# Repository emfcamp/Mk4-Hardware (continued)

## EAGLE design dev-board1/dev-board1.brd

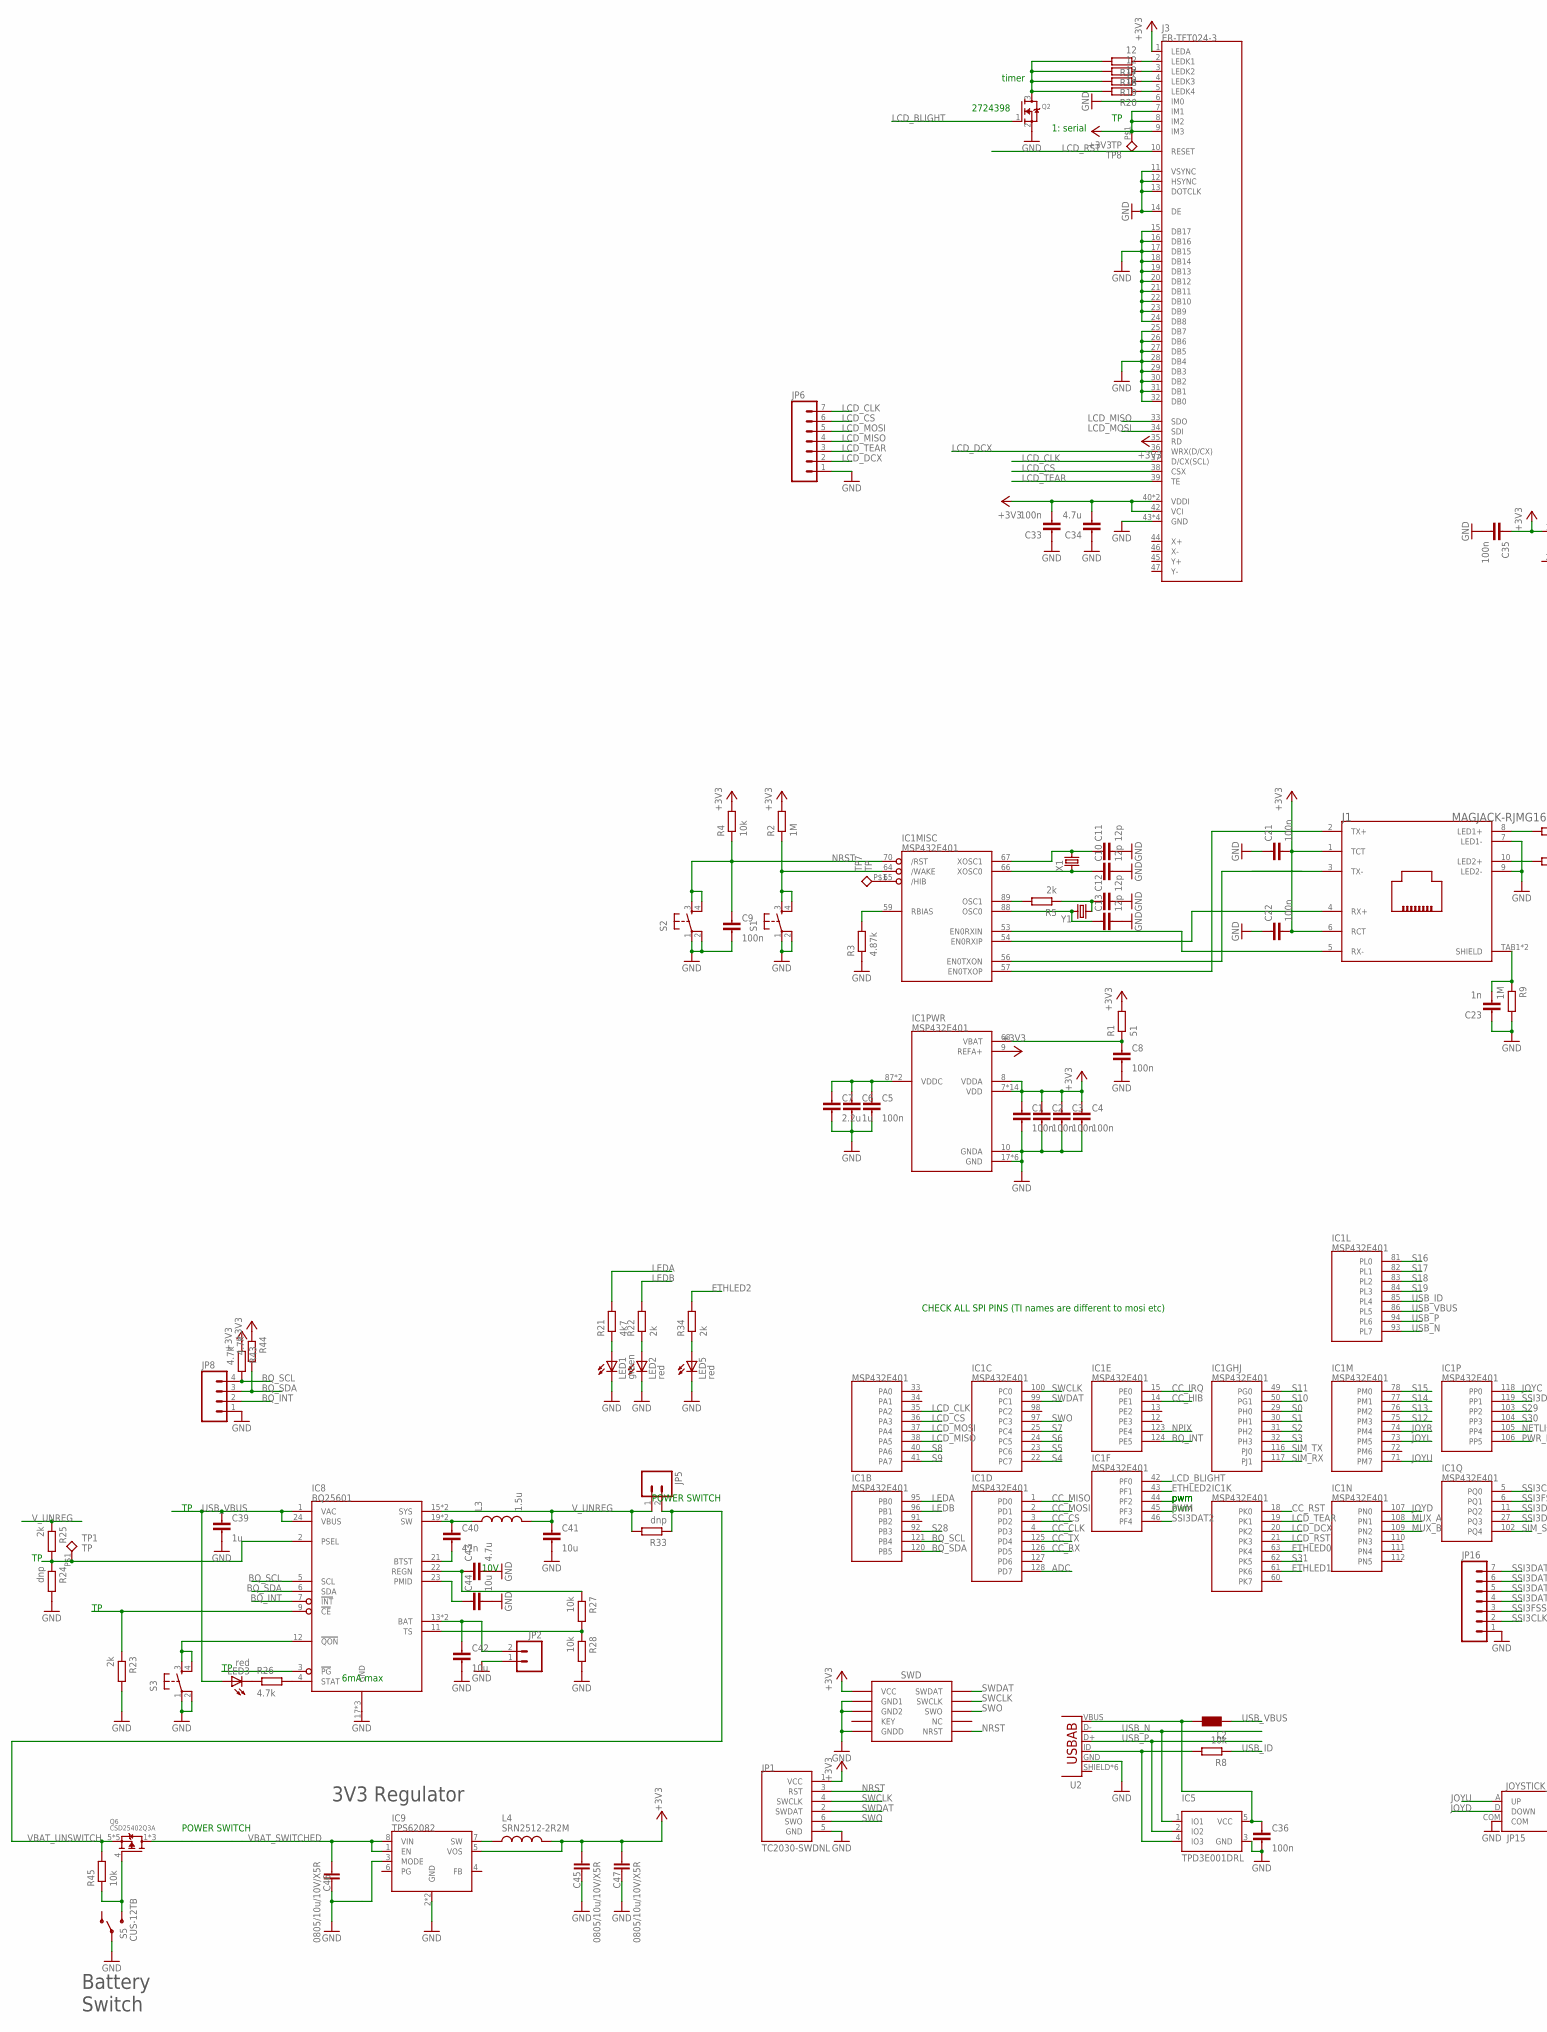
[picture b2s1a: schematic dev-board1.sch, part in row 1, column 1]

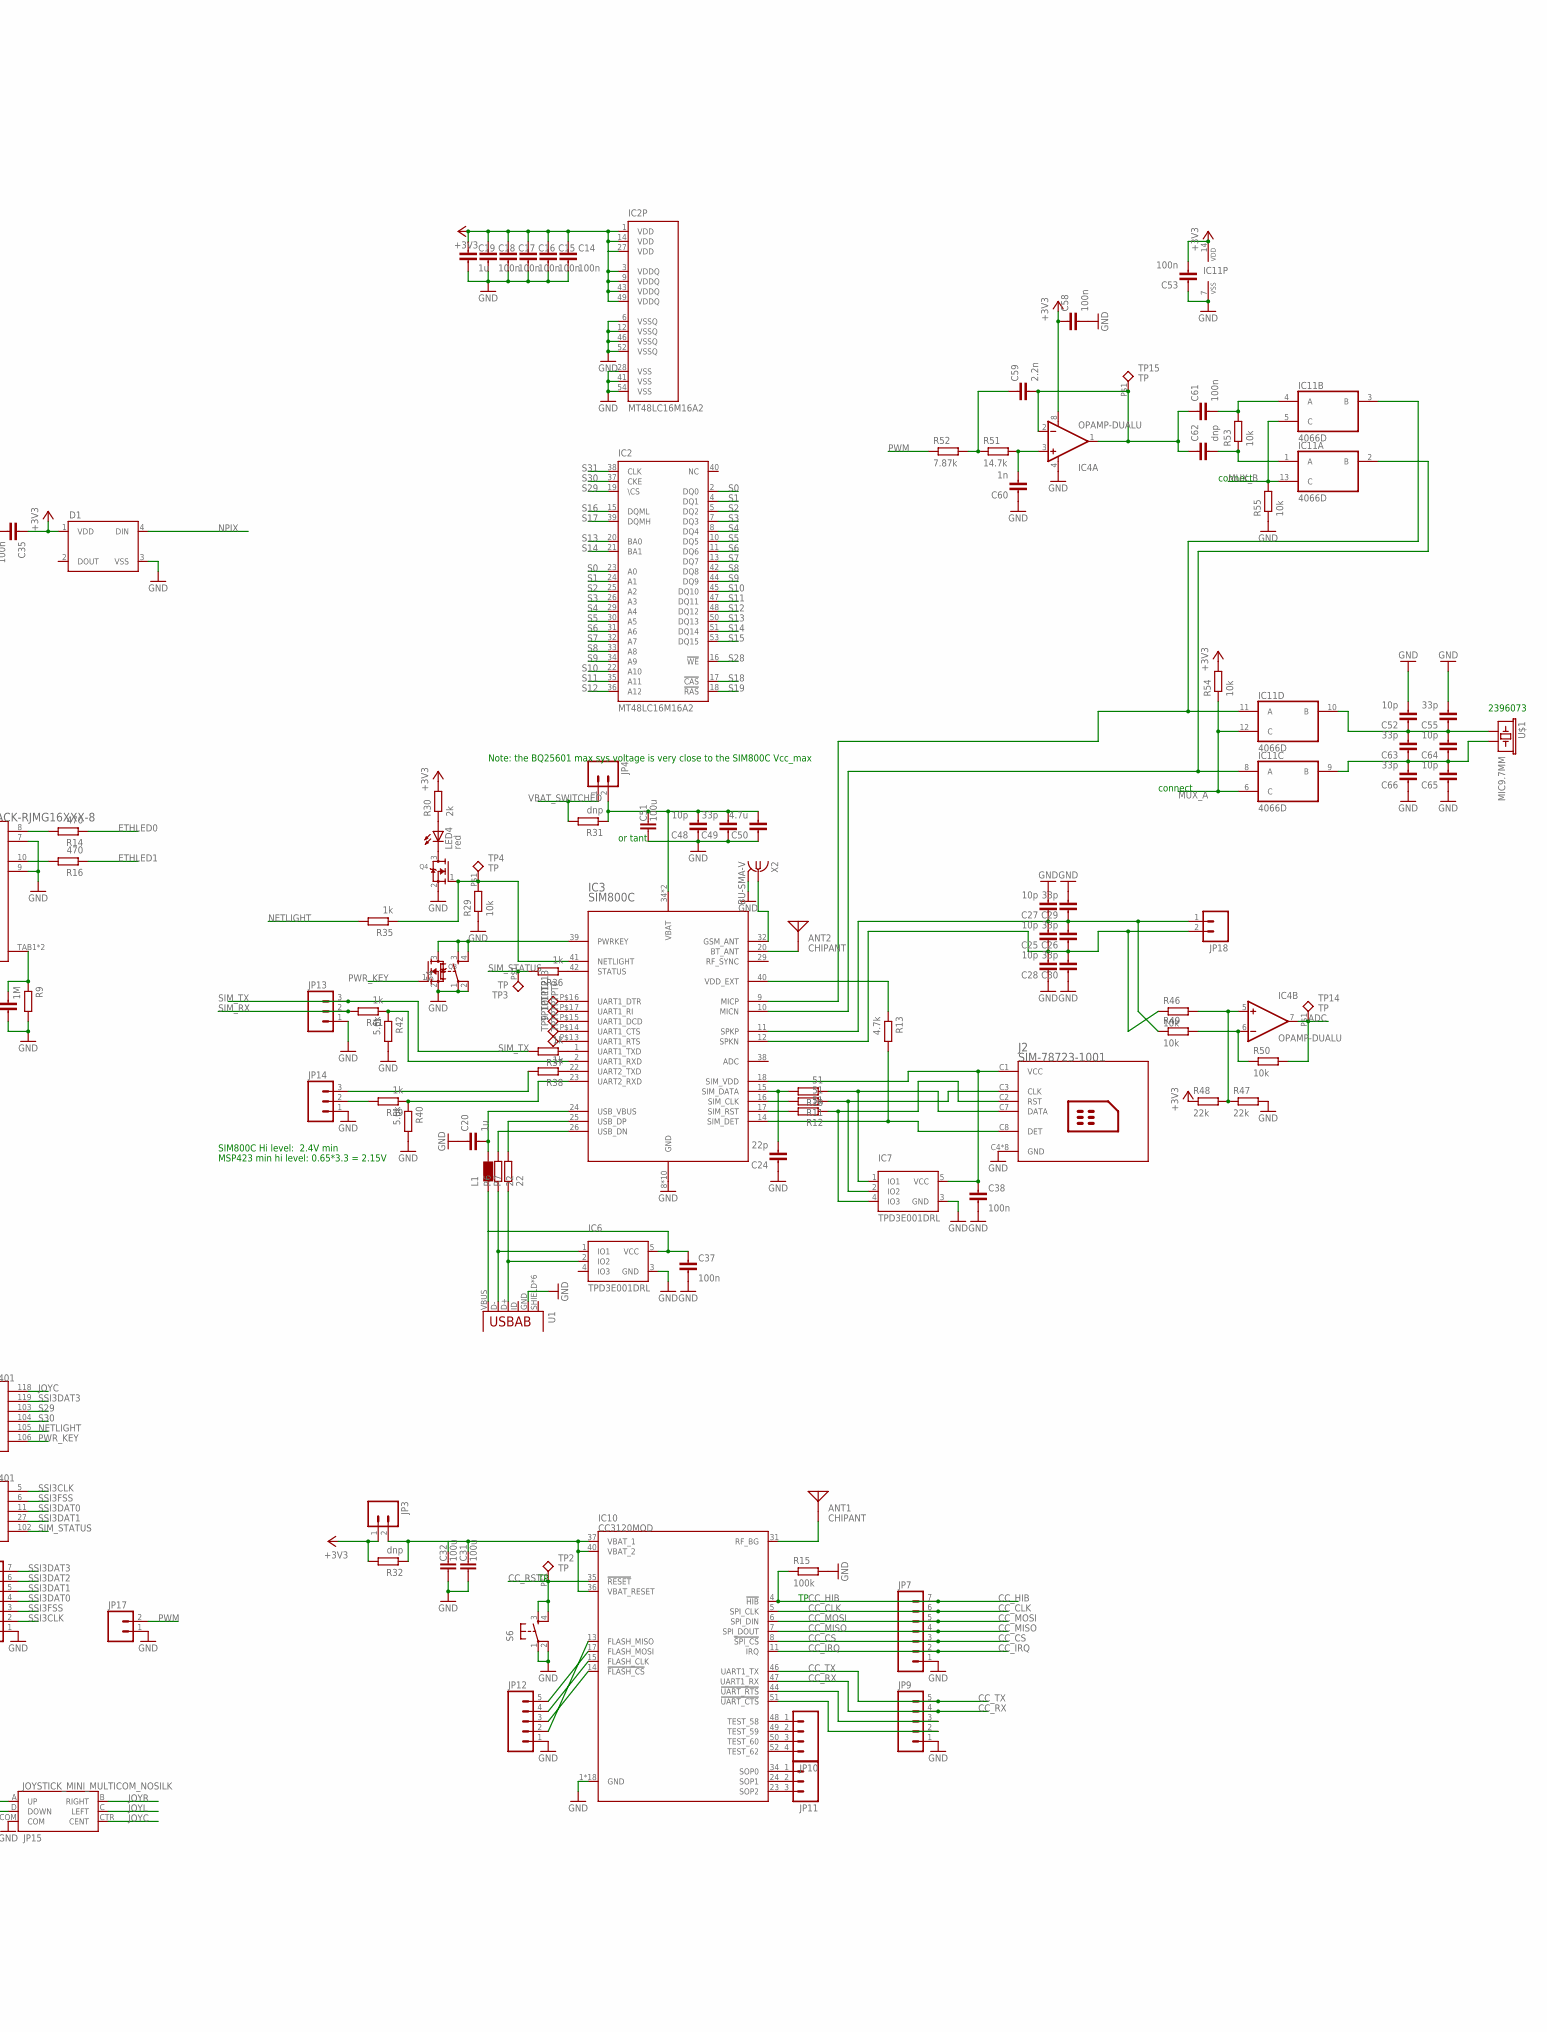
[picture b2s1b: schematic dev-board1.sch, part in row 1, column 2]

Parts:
ANT1, ANT2: CHIPANT; 2450AT42A100; FARNELL 2148522
C1, C2, C3, C4, C5, C8, C9, C14, C15, C16, C17, C18, C21, C22, C33, C35, C36, C37, C38, C53, C58, C61: 100n; C0603-N
C6, C19, C20, C39: 1u; C0603-N
C7: 2.2u; C0603-N
C10, C11, C12, C13: 12p; C0603-N
C23, C60: 1n; C0603-N
C24: 22p; C0603-N
C25, C27, C28, C48, C52, C64, C65: 10p; C0603-N
C26, C29, C30, C49, C55, C63, C66: 33p; C0603-N
C31, C32, C51: 100u; C1210; FARNELL 1889302
C34, C43, C50: 4.7u; C0603-N; FARNELL 2524873
C40: 47n; C0603-N
C41, C42, C44: 10u; C0805-N; FARNELL 2112853/2362101/2576756
C45, C46, C47: 0805/10u/10V/X5R; C0805-N; FARNELL 2112853/2362101/2576756
C59: 2.2n; C0603-N
C62: dnp; C0603-N
D1: WS2812B
IC1: MSP432E401; QFP128-0.4
IC2: MT48LC16M16A2; TSOP54-400; FARNELL 2253738
IC3: SIM800C
IC4: OPAMP-DUALU; SO08; FARNELL 2463666
IC5, IC6, IC7: TPD3E001DRL; DRL-5
IC8: BQ25601; QFN-24
IC9: TPS62082; WSON8; FARNELL 2064227
IC10: CC3120MOD; CC3100MOD-LWK
IC11: 4066D; SO14; FARNELL 1201330
J1: MAGJACK-RJMG16XXX-8; RJMG163118101NR; FARNELL 1357436
J2: SIM-78723-1001; MSIM-MOLEX; FARNELL 2213306
J3: ER-TFT024-3; FH12-50S-0.5SH
J4: SWD_SHROUD; SWD_PTH_SHROUD; FARNELL 1865285
JP1: TC2030-SWDNL; TC2030-MCP-NL
JP2: M02-JST-2MM-SMT; JST-2-SMD; FARNELL 9492615
JP3, JP4, JP5, JP17, JP18: M02PTH; 1X02
JP6, JP7, JP16: M07; 1X07
JP8, JP10: M04PTH; 1X04
JP9, JP12: M05PTH; 1X05
JP11, JP13, JP14: M03PTH; 1X03
JP15: JOYSTICK_MINI_MULTICOM_NOSILK; JOYSTICK_MULTICOMP_NOSILK; FARNELL 1316987
L1, L2: WE-CBF_0805; WUERTH-0805; FARNELL 1781089
L3: 1.5u; 1008; FARNELL 2428202
L4: SRN2512-2R2M; 1008; FARNELL 2428203
LED1: green; LED-0603; FARNELL 2426215
LED2, LED3, LED4, LED5: red; LED-0603; FARNELL 2449874
Q2: MOSFET-N-SOT23-SPARK; SOT23-3; FARNELL 2724398
Q3, Q4: MOSFET-N-SOT23-SPARK; SOT23-3
Q6: CSD25402Q3A; Q3A; FARNELL 2501103
R1, R10, R11, R12: 51; R0603-N
R2, R9: 1M; R0603-N
R3: 4.87k; R0603-N; FARNELL 2447387
R4, R8, R27, R28, R29, R45, R46, R49, R50, R53, R54, R55: 10k; R0603-N
R5, R22, R23, R25, R30, R34: 2k; R0603-N
R6, R7: 22; R0603-N
R13, R26, R43, R44: 4.7k; R0603-N
R14, R16: 470; R0603-N
R15: 100k; R0603-N
R17, R18, R19, R20: 12; R0603-N
R21: 4k7; R0603-N
R24, R31, R32, R33: dnp; R0603-N
R35, R36, R37, R38, R39, R41: 1k; R0603-N
R40, R42: 5.6k; R0603-N
R47, R48: 22k; R0603-N
R51: 14.7k; R0603-N
R52: 7.87k; R0603-N
S1, S2, S3, S4, S6: 6MMTACTSMSM; 6MMTACTSM; FARNELL 2320087
S5: CUS-12TB; SWITCH-SPST-SMD-A; FARNELL 9575146
TP1, TP2, TP3, TP4, TP7, TP8, TP9, TP10, TP11, TP12, TP13, TP14, TP15: TP
U1, U2: USB-AB-LWK; USB-AB-MICRO-SMD_LWK; FARNELL 2293755
U$1: MIC9.7MM; MIC-9.7MM; FARNELL 2396073
X1: RESONATOR_EPSON_FC_145; FARNELL 2723239
X2: BU-SMA-V; FARNELL 1248990
Y1: CRYSTAL5X3; CRYSTAL-SMD-5X3; FARNELL 2508925

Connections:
+3V3: C1.1, C2.1, C3.1, C4.1, C14.1, C15.1, C16.1, C17.1, C18.1, C19.1, C21.2, C22.2, C33.2, C34.2, C35.1, C45.1, C47.1, C53.2, C58.1, D1.1 (VDD), IC1.7 (VDD), IC1.8 (VDDA), IC1.9 (REFA+), IC1.16 (VDD), IC1.26 (VDD), IC1.28 (VDD), IC1.39 (VDD), IC1.47 (VDD), IC1.51 (VDD), IC1.52 (VDD), IC1.69 (VDD), IC1.79 (VDD), IC1.90 (VDD), IC1.101 (VDD), IC1.113 (VDD), IC1.122 (VDD), IC2.1 (VDD), IC2.3 (VDDQ), IC2.9 (VDDQ), IC2.14 (VDD), IC2.27 (VDD), IC2.43 (VDDQ), IC2.49 (VDDQ), IC4.8 (V+), IC9.5 (VOS), IC11.14 (VDD), J1.1 (TCT), J1.6 (RCT), J3.1 (LEDA), J3.7 (IM1), J3.8 (IM2), J3.9 (IM3), J3.35 (RD), J3.40 (VDDI), J3.41 (VDDI), J3.42 (VCI), J4.1 (VCC), JP1.1 (VCC), JP3.1, L4.2, R1.2, R2.2, R4.2, R30.2, R32.2, R43.1, R44.1, R48.1, R54.2, TP8.P$1
ADC: IC1.128 (PD7), IC4.7 (OUT), R50.2, TP14.P$1
BQ_INT: IC1.124 (PE5), IC8.7 (!INT), JP8.2
BQ_SCL: IC1.121 (PB4), IC8.5 (SCL), JP8.4, R43.2
BQ_SDA: IC1.120 (PB5), IC8.6 (SDA), JP8.3, R44.2
CC_CLK: IC1.4 (PD3), IC10.5 (SPI_CLK), JP7.6
CC_CS: IC1.3 (PD2), IC10.8 (!SPI_CS), JP7.3
CC_HIB: IC1.14 (PE1), IC10.4 (!HIB), JP7.7, R15.1
CC_IRQ: IC1.15 (PE0), IC10.11 (IRQ), JP7.2
CC_MISO: IC1.1 (PD0), IC10.7 (SPI_DOUT), JP7.4
CC_MOSI: IC1.2 (PD1), IC10.6 (SPI_DIN), JP7.5
CC_RST: IC1.18 (PK0), IC10.35 (!RESET), S6.3, S6.4, TP2.P$1
CC_RX: IC1.126 (PD5), IC10.47 (UART1_RX), JP9.4
CC_TX: IC1.125 (PD4), IC10.46 (UART1_TX), JP9.5
ETHLED0: IC1.63 (PK4), R14.1
ETHLED1: IC1.61 (PK6), R16.1
ETHLED2: IC1.43 (PF1), R34.2
GGGG: IC3.2 (UART1_RXD), R41.1, R42.1
GND: C1.2, C2.2, C3.2, C4.2, C5.2, C6.2, C7.2, C8.2, C9.2, C10.2, C11.2, C12.2, C13.2, C14.2, C15.2, C16.2, C17.2, C18.2, C19.2, C20.1, C21.1, C22.1, C23.1, C24.1, C27.2, C28.1, C29.2, C30.1, C31.2, C32.2, C33.1, C34.1, C35.2, C36.2, C37.2, C38.2, C39.2, C41.2, C42.2, C43.2, C44.2, C45.2, C46.2, C47.2, C48.1, C49.1, C50.1, C51.2, C52.2, C53.1, C55.2, C58.2, C60.1, C65.1, C66.1, D1.3 (VSS), IC1.10 (GNDA), IC1.17 (GND), IC1.48 (GND), IC1.55 (GND), IC1.58 (GND), IC1.80 (GND), IC1.114 (GND), IC2.6 (VSSQ), IC2.12 (VSSQ), IC2.28 (VSS), IC2.41 (VSS), IC2.46 (VSSQ), IC2.52 (VSSQ), IC2.54 (VSS), IC3.8 (GND), IC3.13 (GND), IC3.19 (GND), IC3.21 (GND), IC3.27 (GND), IC3.30 (GND), IC3.31 (GND), IC3.33 (GND), IC3.36 (GND), IC3.37 (GND), IC4.4 (V-), IC5.3 (GND), IC6.3 (GND), IC7.3 (GND), IC8.17 (GND), IC8.18 (GND), IC8.25 (GND), IC9.2 (GND), IC9.3 (MODE), IC9.EP (GND), IC10.1 (GND), IC10.2 (GND), IC10.16 (GND), IC10.27 (GND), IC10.28 (GND), IC10.30 (GND), IC10.32 (GND), IC10.38 (GND), IC10.43 (GND), IC10.55 (GND), IC10.56 (GND), IC10.57 (GND), IC10.58 (GND), IC10.59 (GND), IC10.60 (GND), IC10.61 (GND), IC10.62 (GND), IC10.63 (GND), IC11.7 (VSS), J1.7 (LED1-), J1.9 (LED2-), J2.C4 (GND), J2.C5 (GND), J2.GND1 (GND), J2.GND2 (GND), J2.GND3 (GND), J2.GND4 (GND), J2.GND5 (GND), J2.GND6 (GND), J3.6 (IM0), J3.11 (VSYNC), J3.12 (HSYNC), J3.13 (DOTCLK), J3.14 (DE), J3.15 (DB17), J3.16 (DB16), J3.17 (DB15), J3.18 (DB14), J3.19 (DB13), J3.20 (DB12), J3.21 (DB11), J3.22 (DB10), J3.23 (DB9), J3.24 (DB8), J3.25 (DB7), J3.26 (DB6), J3.27 (DB5), J3.28 (DB4), J3.29 (DB3), J3.30 (DB2), J3.31 (DB1), J3.32 (DB0), J3.43 (GND), J3.48 (GND), J3.49 (GND), J3.50 (GND), J4.3 (GND1), J4.5 (GND2), J4.9 (GNDD), JP1.5 (GND), JP2.1, JP6.1, JP7.1, JP8.1, JP9.1, JP12.1, JP13.1, JP14.1, JP15.COM, JP16.1, JP17.1, LED1.C, LED2.C, LED5.C, Q2.2 (S), Q3.2 (S), Q4.2 (S), R3.1, R9.2, R15.2, R23.2, R24.2, R28.2, R29.1, R40.2, R42.2, R47.2, R55.1, S1.1, S1.2, S2.1, S2.2, S3.1, S3.2, S4.1, S4.2, S5.2, S6.1, S6.2, U1.GND, U2.GND, X2.2, X2.3 (2), X2.4 (2), X2.5 (2)
JOYC: IC1.118 (PP0), JP15.CTR (CENT)
JOYD: IC1.107 (PN0), JP15.D (DOWN)
JOYL: IC1.73 (PM5), JP15.C (LEFT)
JOYR: IC1.74 (PM4), JP15.B (RIGHT)
JOYU: IC1.71 (PM7), JP15.A (UP)
LCD_BLIGHT: IC1.42 (PF0), Q2.1 (G)
LCD_CLK: IC1.35 (PA2), J3.37 (D/CX(SCL)), JP6.7
LCD_CS: IC1.36 (PA3), J3.38 (CSX), JP6.6
LCD_DCX: IC1.20 (PK2), J3.36 (WRX(D/CX)), JP6.2
LCD_MISO: IC1.38 (PA5), J3.33 (SDO), JP6.4
LCD_MOSI: IC1.37 (PA4), J3.34 (SDI), JP6.5
LCD_RST: IC1.21 (PK3), J3.10 (RESET)
LCD_TEAR: IC1.19 (PK1), J3.39 (TE), JP6.3
LEDA: IC1.95 (PB0), R21.2
LEDB: IC1.96 (PB1), R22.2
MUX_A: IC1.108 (PN1), IC11.6 (C), IC11.12 (C), R54.1
MUX_B: IC1.109 (PN2), IC11.5 (C), IC11.13 (C), R55.2
unnamed: IC1.89 (OSC1), R5.2
unnamed: C5.1, C6.1, C7.1, IC1.87 (VDDC), IC1.115 (VDDC)
unnamed: C42.1, IC8.13 (BAT), IC8.14 (BAT), JP2.2
unnamed: C12.1, R5.1, Y1.1
unnamed: C13.1, IC1.88 (OSC0), Y1.3 (2)
unnamed: C10.1, IC1.66 (XOSC0), X1.P$1 (1)
unnamed: C8.1, IC1.68 (VBAT), R1.1
unnamed: C11.1, IC1.67 (XOSC1), X1.P$2 (2)
unnamed: IC1.64 (/WAKE), R2.1, S1.3, S1.4
unnamed: IC6.1 (IO1), R6.1, U1.D-
unnamed: IC1.59 (RBIAS), R3.2
unnamed: IC3.32 (GSM_ANT), X2.1
unnamed: IC6.2 (IO2), R7.1, U1.D+
unnamed: IC3.25 (USB_DP), R7.2
unnamed: IC3.26 (USB_DN), R6.2
unnamed: IC5.4 (IO3), R8.2, U2.ID (USBID)
unnamed: C36.1, IC5.5 (VCC), L2.2, U2.VBUS
unnamed: C20.2, IC3.24 (USB_VBUS), L1.2
unnamed: C37.1, IC6.5 (VCC), L1.1, U1.VBUS
unnamed: IC1.53 (EN0RXIN), J1.5 (RX-)
unnamed: IC1.54 (EN0RXIP), J1.4 (RX+)
unnamed: IC1.56 (EN0TXON), J1.3 (TX-)
unnamed: IC1.57 (EN0TXOP), J1.2 (TX+)
unnamed: C23.2, J1.TAB1 (SHIELD), J1.TAB2 (SHIELD), R9.1
unnamed: J1.8 (LED1+), R14.2
unnamed: J1.10 (LED2+), R16.2
unnamed: C24.2, IC3.15 (SIM_DATA), R10.2
unnamed: IC3.16 (SIM_CLK), R11.2
unnamed: IC3.17 (SIM_RST), R12.2
unnamed: IC7.1 (IO1), J2.C7 (DATA), R10.1
unnamed: IC7.2 (IO2), J2.C3 (CLK), R11.1
unnamed: IC7.4 (IO3), J2.C2 (RST), R12.1
unnamed: IC3.14 (SIM_DET), J2.C8 (DET), R13.2
unnamed: IC3.40 (VDD_EXT), R13.1
unnamed: C38.1, IC3.18 (SIM_VDD), IC7.5 (VCC), J2.C1 (VCC)
unnamed: IC4.5 (+IN), R46.2, R47.1, R48.2
unnamed: IC3.9 (MICP), IC11.3 (B), IC11.11 (A)
unnamed: LED5.A, R34.1
unnamed: C25.2, C26.2, C27.1, C29.1, IC3.11 (SPKP), JP18.1, R49.1
unnamed: C25.1, C26.1, C28.2, C30.2, IC3.12 (SPKN), JP18.2, R46.1
unnamed: IC3.10 (MICN), IC11.2 (B), IC11.8 (A)
unnamed: IC10.48 (TEST_58), JP10.1
unnamed: IC10.44 (!UART_RTS), JP9.3
unnamed: C48.2, C49.2, C50.2, C51.1, IC3.34 (VBAT), IC3.35 (VBAT), JP4.2, R31.1
unnamed: LED4.C, Q4.3 (D)
unnamed: ANT1.P$1, IC10.31 (RF_BG)
unnamed: IC10.51 (!UART_CTS), JP9.2
unnamed: C31.1, C32.1, IC10.36 (VBAT_RESET), IC10.37 (VBAT_1), IC10.40 (VBAT_2), JP3.2, R32.1
unnamed: IC10.49 (TEST_59), JP10.2
unnamed: IC10.50 (TEST_60), JP10.3
unnamed: IC3.39 (PWRKEY), Q3.3 (D), S4.3, S4.4
unnamed: IC10.52 (TEST_62), JP10.4
unnamed: IC10.34 (SOP0), JP11.1
unnamed: J3.2 (LEDK1), R17.1
unnamed: J3.3 (LEDK2), R18.1
unnamed: J3.4 (LEDK3), R19.1
unnamed: J3.5 (LEDK4), R20.1
unnamed: Q2.3 (D), R17.2, R18.2, R19.2, R20.2
unnamed: IC10.24 (SOP1), JP11.2
unnamed: ANT2.P$1, IC3.20 (BT_ANT)
unnamed: C40.1, IC8.19 (SW), IC8.20 (SW), L3.1
unnamed: LED4.A, R30.1
unnamed: IC10.23 (SOP2), JP11.3
unnamed: IC10.15 (FLASH_CLK), JP12.4
unnamed: LED1.A, R21.1
unnamed: LED2.A, R22.1
unnamed: IC10.14 (!FLASH_CS), JP12.3
unnamed: IC10.17 (FLASH_MOSI), JP12.5
unnamed: IC10.13 (FLASH_MISO), JP12.2
unnamed: IC3.22 (UART2_TXD), R38.1
unnamed: C40.2, IC8.21 (BTST)
unnamed: C43.1, IC8.22 (REGN), R27.1
unnamed: C44.1, IC8.23 (PMID)
unnamed: IC8.12 (!QON), S3.3, S3.4
unnamed: JP14.3, R38.2
unnamed: IC8.9 (!CE), R23.1
unnamed: IC8.2 (PSEL), R24.1, R25.2, TP1.P$1
unnamed: IC1.65 (/HIB), TP7.P$1
unnamed: C63.1, C64.1, C65.2, C66.2, IC11.9 (B), U$1.2
unnamed: IC3.42 (STATUS), R36.1
unnamed: IC8.4 (STAT), R26.2
unnamed: LED3.C, R26.1
unnamed: IC8.11 (TS), R27.2, R28.1
unnamed: IC4.6 (-IN), R49.2, R50.1
unnamed: C59.2, C61.1, C62.1, IC4.1 (OUT), IC4.2 (-IN), TP15.P$1
unnamed: IC3.1 (UART1_TXD), R37.1
unnamed: IC3.23 (UART2_RXD), R39.1, R40.1
unnamed: JP14.2, R39.2
unnamed: IC3.3 (UART1_RTS), TP9.P$1
unnamed: IC3.4 (UART1_CTS), TP10.P$1
unnamed: IC3.5 (UART1_DCD), TP11.P$1
unnamed: IC3.7 (UART1_RI), TP12.P$1
unnamed: IC3.6 (UART1_DTR), TP13.P$1
unnamed: C60.2, IC4.3 (+IN), R51.2
unnamed: C59.1, R51.1, R52.2
unnamed: C61.2, IC11.4 (A), R53.2
unnamed: C62.2, IC11.1 (A), R53.1
unnamed: C52.1, C55.1, C63.2, C64.2, IC11.10 (B), U$1.1
NETLIGHT: IC1.105 (PP4), R35.2
NETLIGHT_: IC3.41 (NETLIGHT), Q4.1 (G), R29.2, R35.1, TP4.P$1
NPIX: D1.4 (DIN), IC1.123 (PE4)
NRST: C9.1, IC1.70 (/RST), J4.10 (NRST), JP1.3 (RST), R4.1, S2.3, S2.4
PWM: IC1.45 (PF3), JP17.2, R52.1
PWR_KEY: IC1.106 (PP5), Q3.1 (G)
S0: IC1.29 (PH0), IC2.2 (DQ0), IC2.23 (A0)
S1: IC1.30 (PH1), IC2.4 (DQ1), IC2.24 (A1)
S2: IC1.31 (PH2), IC2.5 (DQ2), IC2.25 (A2)
S3: IC1.32 (PH3), IC2.7 (DQ3), IC2.26 (A3)
S4: IC1.22 (PC7), IC2.8 (DQ4), IC2.29 (A4)
S5: IC1.23 (PC6), IC2.10 (DQ5), IC2.30 (A5)
S6: IC1.24 (PC5), IC2.11 (DQ6), IC2.31 (A6)
S7: IC1.25 (PC4), IC2.13 (DQ7), IC2.32 (A7)
S8: IC1.40 (PA6), IC2.33 (A8), IC2.42 (DQ8)
S9: IC1.41 (PA7), IC2.34 (A9), IC2.44 (DQ9)
S10: IC1.50 (PG1), IC2.22 (A10), IC2.45 (DQ10)
S11: IC1.49 (PG0), IC2.35 (A11), IC2.47 (DQ11)
S12: IC1.75 (PM3), IC2.36 (A12), IC2.48 (DQ12)
S13: IC1.76 (PM2), IC2.20 (BA0), IC2.50 (DQ13)
S14: IC1.77 (PM1), IC2.21 (BA1), IC2.51 (DQ14)
S15: IC1.78 (PM0), IC2.53 (DQ15)
S16: IC1.81 (PL0), IC2.15 (DQML)
S17: IC1.82 (PL1), IC2.39 (DQMH)
S18: IC1.83 (PL2), IC2.17 (!CAS)
S19: IC1.84 (PL3), IC2.18 (!RAS)
S28: IC1.92 (PB3), IC2.16 (!WE)
S29: IC1.103 (PP2), IC2.19 (\CS)
S30: IC1.104 (PP3), IC2.37 (CKE)
S31: IC1.62 (PK5), IC2.38 (CLK)
SIM_RX: IC1.117 (PJ1), JP13.2, R41.2
SIM_STATUS: IC1.102 (PQ4), R36.2, TP3.P$1
SIM_TX: IC1.116 (PJ0), JP13.3, R37.2
SSI3CLK: IC1.5 (PQ0), JP16.2
SSI3DAT0: IC1.11 (PQ2), JP16.4
SSI3DAT1: IC1.27 (PQ3), JP16.5
SSI3DAT2: IC1.46 (PF4), JP16.6
SSI3DAT3: IC1.119 (PP1), JP16.7
SSI3FSS: IC1.6 (PQ1), JP16.3
SW: IC9.7 (SW), L4.1
SWCLK: IC1.100 (PC0), J4.4 (SWCLK), JP1.4 (SWCLK)
SWDAT: IC1.99 (PC1), J4.2 (SWDAT), JP1.2 (SWDAT)
SWO: IC1.97 (PC3), J4.6 (SWO), JP1.6 (SWO)
USB_ID: IC1.85 (PL4), R8.1
USB_N: IC1.93 (PL7), IC5.1 (IO1), U2.D-
USB_P: IC1.94 (PL6), IC5.2 (IO2), U2.D+
USB_VBUS: C39.1, IC1.86 (PL5), IC8.1 (VAC), IC8.24 (VBUS), L2.1, LED3.A
VBAT_SWITCHED: C46.1, IC9.1 (EN), IC9.8 (VIN), JP4.1, Q6.1 (D), Q6.2 (D), Q6.3 (D), R31.2
VBAT_SWITCH_CONTROL: Q6.4 (G), R45.1, S5.3 (S)
VBAT_UNSWITCH: JP5.2, Q6.5 (S), Q6.6 (S), Q6.7 (S), Q6.8 (S), Q6.EP (S), R33.1, R45.2
V_UNREG: C41.1, IC8.15 (SYS), IC8.16 (SYS), JP5.1, L3.2, R25.1, R33.2

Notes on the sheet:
timer
1: serial
3V3 Regulator
10V
6mA max
POWER SWITCH
Battery Switch
CHECK ALL SPI PINS (TI names are different to mosi etc)
or tant
2396073
2724398
SIM800C Hi level: 2.4V min
MSP423 min hi level: 0.65*3.3 = 2.15V
Note: the BQ25601 max sys voltage is very close to the SIM800C Vcc_max
pwm
connect

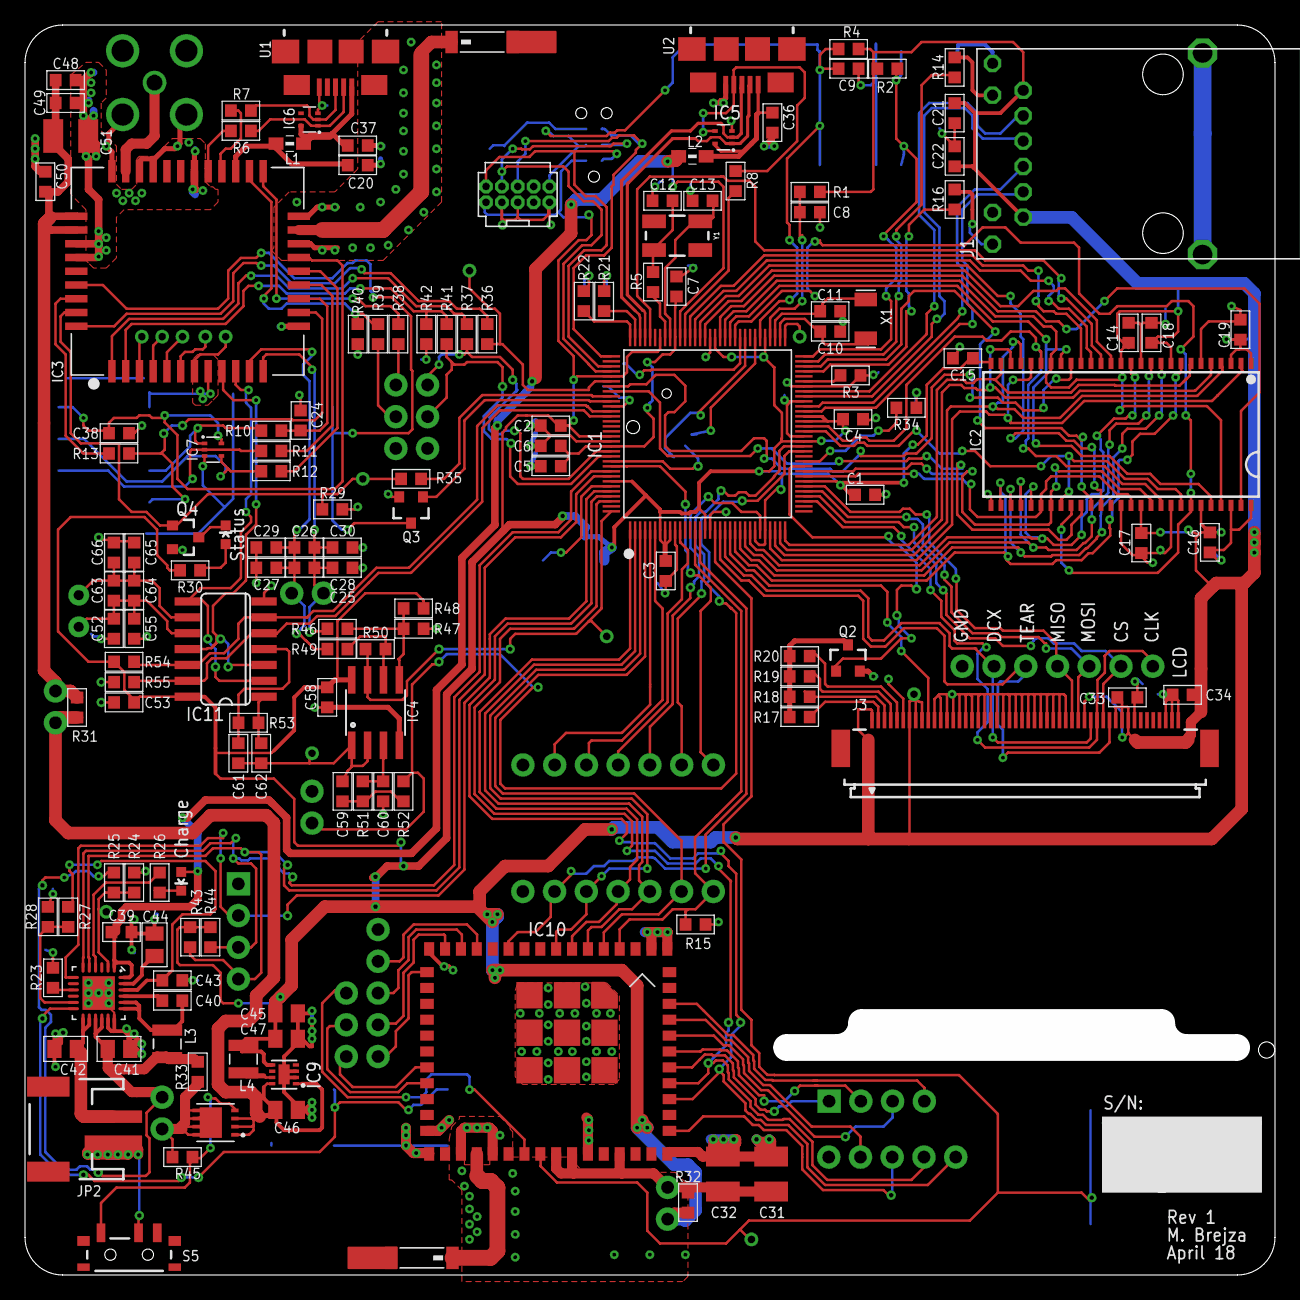
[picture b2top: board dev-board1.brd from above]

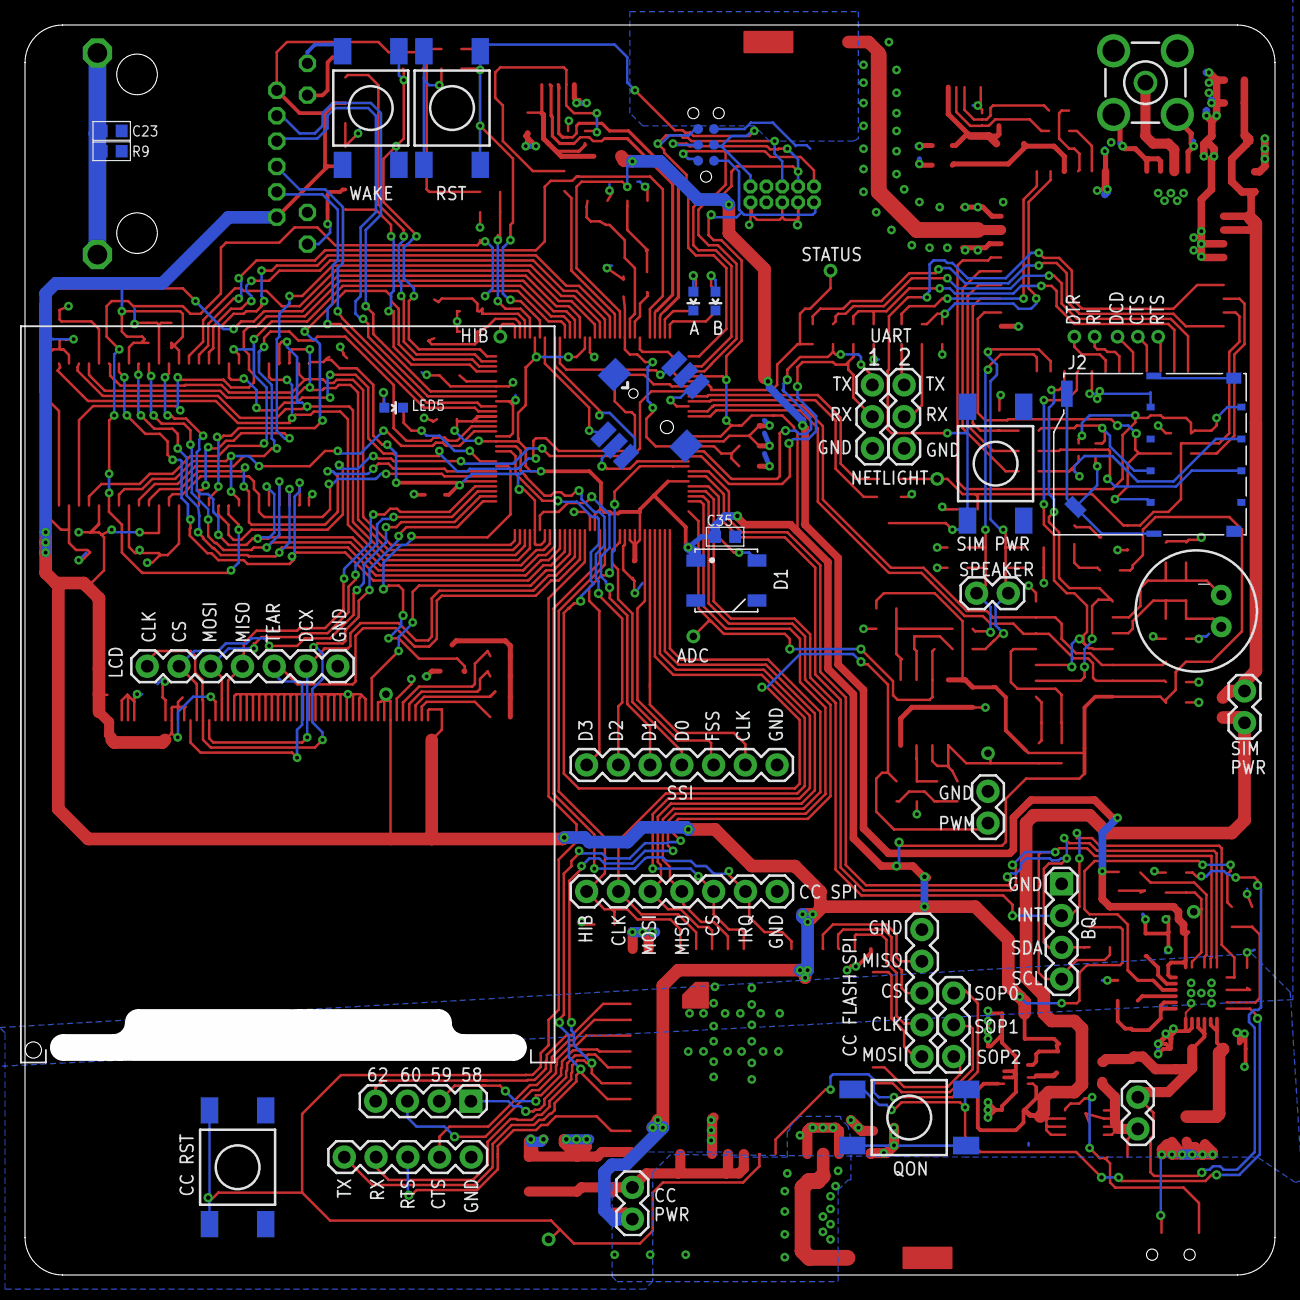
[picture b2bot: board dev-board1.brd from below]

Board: 2 copper layers, 100.0 x 100.0 mm, 193 parts (36 on the bottom side), 185 nets.

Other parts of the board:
U3: ER-TFT024-3-OUTLINE; ER-TFT024-3

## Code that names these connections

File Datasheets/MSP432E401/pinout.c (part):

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	GPIOD->GPIO_O_LOCK = 0x0;
	
    //
    // Configure the GPIO Pin Mux for PD7
	// for AIN4
    //
	MAP_GPIOPinTypeADC(GPIO_PORTD_BASE, GPIO_PIN_7);
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	GPIOPinTypeEPI(GPIO_PORTL_BASE, GPIO_PIN_0);

    //
    // Configure the GPIO Pin Mux for PG0
	// for EPI0S11
    //
	MAP_GPIOPinConfigure(GPIO_PG0_EPI0S11);
	GPIOPinTypeEPI(GPIO_PORTG_BASE, GPIO_PIN_0);

    //
    // Configure the GPIO Pin Mux for PA6
	// for EPI0S8
    //
	MAP_GPIOPinConfigure(GPIO_PA6_EPI0S8);
	GPIOPinTypeEPI(GPIO_PORTA_BASE, GPIO_PIN_6);

    //
    // Configure the GPIO Pin Mux for PH1
	// for EPI0S1
    //
	MAP_GPIOPinConfigure(GPIO_PH1_EPI0S1);
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	GPIOPinTypeEPI(GPIO_PORTM_BASE, GPIO_PIN_2);

    //
    // Configure the GPIO Pin Mux for PB3
	// for EPI0S28
    //
	MAP_GPIOPinConfigure(GPIO_PB3_EPI0S28);
	GPIOPinTypeEPI(GPIO_PORTB_BASE, GPIO_PIN_3);

    //
    // Configure the GPIO Pin Mux for PG1
	// for EPI0S10
    //
	MAP_GPIOPinConfigure(GPIO_PG1_EPI0S10);
	GPIOPinTypeEPI(GPIO_PORTG_BASE, GPIO_PIN_1);

    //
    // Configure the GPIO Pin Mux for PK5
	// for EPI0S31
    //
	MAP_GPIOPinConfigure(GPIO_PK5_EPI0S31);
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	GPIOPinTypeEPI(GPIO_PORTP_BASE, GPIO_PIN_2);

    //
    // Configure the GPIO Pin Mux for PH3
	// for EPI0S3
    //
	MAP_GPIOPinConfigure(GPIO_PH3_EPI0S3);
	GPIOPinTypeEPI(GPIO_PORTH_BASE, GPIO_PIN_3);

    //
    // Configure the GPIO Pin Mux for PC5
	// for EPI0S6
    //
	MAP_GPIOPinConfigure(GPIO_PC5_EPI0S6);
	GPIOPinTypeEPI(GPIO_PORTC_BASE, GPIO_PIN_5);

    //
    // Configure the GPIO Pin Mux for PA7
	// for EPI0S9
    //
	MAP_GPIOPinConfigure(GPIO_PA7_EPI0S9);
	GPIOPinTypeEPI(GPIO_PORTA_BASE, GPIO_PIN_7);

    //
    // Configure the GPIO Pin Mux for PH0
	// for EPI0S0
    //
	MAP_GPIOPinConfigure(GPIO_PH0_EPI0S0);
	GPIOPinTypeEPI(GPIO_PORTH_BASE, GPIO_PIN_0);

    //
    // Configure the GPIO Pin Mux for PC4
	// for EPI0S7
    //
	MAP_GPIOPinConfigure(GPIO_PC4_EPI0S7);
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	GPIOPinTypeEPI(GPIO_PORTM_BASE, GPIO_PIN_1);

    //
    // Configure the GPIO Pin Mux for PC7
	// for EPI0S4
    //
	MAP_GPIOPinConfigure(GPIO_PC7_EPI0S4);
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	GPIOPinTypeEPI(GPIO_PORTM_BASE, GPIO_PIN_3);

    //
    // Configure the GPIO Pin Mux for PC6
	// for EPI0S5
    //
	MAP_GPIOPinConfigure(GPIO_PC6_EPI0S5);
	GPIOPinTypeEPI(GPIO_PORTC_BASE, GPIO_PIN_6);

    //
    // Configure the GPIO Pin Mux for PH2
	// for EPI0S2
    //
	MAP_GPIOPinConfigure(GPIO_PH2_EPI0S2);
	GPIOPinTypeEPI(GPIO_PORTH_BASE, GPIO_PIN_2);

    //
    // Configure the GPIO Pin Mux for PK4
	// for EN0LED0
    //
	MAP_GPIOPinConfigure(GPIO_PK4_EN0LED0);
	GPIOPinTypeEthernetLED(GPIO_PORTK_BASE, GPIO_PIN_4);

    //
    // Configure the GPIO Pin Mux for PK6
	// for EN0LED1
    //
	MAP_GPIOPinConfigure(GPIO_PK6_EN0LED1);
	GPIOPinTypeEthernetLED(GPIO_PORTK_BASE, GPIO_PIN_6);

    //
    // Configure the GPIO Pin Mux for PE5
	// for GPIO_PE5
    //
	MAP_GPIOPinTypeGPIOOutput(GPIO_PORTE_BASE, GPIO_PIN_5);

    //
    // Configure the GPIO Pin Mux for PE4
	// for GPIO_PE4
    //
	MAP_GPIOPinTypeGPIOInput(GPIO_PORTE_BASE, GPIO_PIN_4);

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	MAP_GPIOPinTypeGPIOOutput(GPIO_PORTP_BASE, GPIO_PIN_0);

    //
    // Configure the GPIO Pin Mux for PE1
	// for GPIO_PE1
    //
	MAP_GPIOPinTypeGPIOInput(GPIO_PORTE_BASE, GPIO_PIN_1);

    //
    // Configure the GPIO Pin Mux for PE0
	// for GPIO_PE0
    //
	MAP_GPIOPinTypeGPIOInput(GPIO_PORTE_BASE, GPIO_PIN_0);

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	GPIOC->GPIO_O_LOCK = 0x0;
	
    //
    // Configure the GPIO Pin Mux for PC0
	// for GPIO_PC0
    //
	MAP_GPIOPinTypeGPIOInput(GPIO_PORTC_BASE, GPIO_PIN_0);

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	GPIOC->GPIO_O_LOCK = 0x0;
	
    //
    // Configure the GPIO Pin Mux for PC1
	// for GPIO_PC1
    //
	MAP_GPIOPinTypeGPIOInput(GPIO_PORTC_BASE, GPIO_PIN_1);

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	GPIOC->GPIO_O_LOCK = 0x0;
	
    //
    // Configure the GPIO Pin Mux for PC3
	// for GPIO_PC3
    //
	MAP_GPIOPinTypeGPIOOutput(GPIO_PORTC_BASE, GPIO_PIN_3);

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	MAP_GPIOPinTypeGPIOOutput(GPIO_PORTL_BASE, GPIO_PIN_4);

    //
    // Configure the GPIO Pin Mux for PK3
	// for GPIO_PK3
    //
	MAP_GPIOPinTypeGPIOInput(GPIO_PORTK_BASE, GPIO_PIN_3);

    //
    // Configure the GPIO Pin Mux for PK2
	// for GPIO_PK2
    //
	MAP_GPIOPinTypeGPIOOutput(GPIO_PORTK_BASE, GPIO_PIN_2);

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	MAP_GPIOPadConfigSet(GPIO_PORTK_BASE, GPIO_PIN_7, GPIO_STRENGTH_2MA, GPIO_PIN_TYPE_STD_WPU);

    //
    // Configure the GPIO Pin Mux for PF1
	// for GPIO_PF1
    //
	MAP_GPIOPinTypeGPIOInput(GPIO_PORTF_BASE, GPIO_PIN_1);

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	MAP_GPIOPinTypeGPIOOutput(GPIO_PORTN_BASE, GPIO_PIN_3);

    //
    // Configure the GPIO Pin Mux for PD5
	// for GPIO_PD5
    //
	MAP_GPIOPinTypeGPIOInput(GPIO_PORTD_BASE, GPIO_PIN_5);

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	MAP_GPIOPinTypeGPIOInput(GPIO_PORTQ_BASE, GPIO_PIN_4);

    //
    // Configure the GPIO Pin Mux for PB4
	// for I2C5SCL
    //
	MAP_GPIOPinConfigure(GPIO_PB4_I2C5SCL);
	MAP_GPIOPinTypeI2CSCL(GPIO_PORTB_BASE, GPIO_PIN_4);

    //
    // Configure the GPIO Pin Mux for PB5
	// for I2C5SDA
    //
	MAP_GPIOPinConfigure(GPIO_PB5_I2C5SDA);
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	MAP_GPIOPinTypeI2C(GPIO_PORTA_BASE, GPIO_PIN_1);

    //
    // Configure the GPIO Pin Mux for PF0
	// for M0PWM0
    //
	MAP_GPIOPinConfigure(GPIO_PF0_M0PWM0);
	MAP_GPIOPinTypePWM(GPIO_PORTF_BASE, GPIO_PIN_0);

    //
    // Configure the GPIO Pin Mux for PF3
	// for M0PWM3
    //
	MAP_GPIOPinConfigure(GPIO_PF3_M0PWM3);
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	MAP_GPIOPinTypeSSI(GPIO_PORTQ_BASE, GPIO_PIN_1);

    //
    // Configure the GPIO Pin Mux for PF4
	// for SSI3XDAT2
    //
	MAP_GPIOPinConfigure(GPIO_PF4_SSI3XDAT2);
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	MAP_GPIOPinTypeSSI(GPIO_PORTQ_BASE, GPIO_PIN_0);

    //
    // Configure the GPIO Pin Mux for PD1
	// for SSI2XDAT0
    //
	MAP_GPIOPinConfigure(GPIO_PD1_SSI2XDAT0);
	MAP_GPIOPinTypeSSI(GPIO_PORTD_BASE, GPIO_PIN_1);

    //
    // Configure the GPIO Pin Mux for PD0
	// for SSI2XDAT1
    //
	MAP_GPIOPinConfigure(GPIO_PD0_SSI2XDAT1);
	MAP_GPIOPinTypeSSI(GPIO_PORTD_BASE, GPIO_PIN_0);

    //
    // Configure the GPIO Pin Mux for PD2
	// for SSI2FSS
    //
	MAP_GPIOPinConfigure(GPIO_PD2_SSI2FSS);
	MAP_GPIOPinTypeSSI(GPIO_PORTD_BASE, GPIO_PIN_2);

    //
    // Configure the GPIO Pin Mux for PD3
	// for SSI2CLK
    //
	MAP_GPIOPinConfigure(GPIO_PD3_SSI2CLK);
	MAP_GPIOPinTypeSSI(GPIO_PORTD_BASE, GPIO_PIN_3);

    //
    // Configure the GPIO Pin Mux for PA4
	// for SSI0XDAT0
    //
	MAP_GPIOPinConfigure(GPIO_PA4_SSI0XDAT0);
	MAP_GPIOPinTypeSSI(GPIO_PORTA_BASE, GPIO_PIN_4);

    //
    // Configure the GPIO Pin Mux for PA5
	// for SSI0XDAT1
    //
	MAP_GPIOPinConfigure(GPIO_PA5_SSI0XDAT1);
	MAP_GPIOPinTypeSSI(GPIO_PORTA_BASE, GPIO_PIN_5);

    //
    // Configure the GPIO Pin Mux for PA3
	// for SSI0FSS
    //
	MAP_GPIOPinConfigure(GPIO_PA3_SSI0FSS);
	MAP_GPIOPinTypeSSI(GPIO_PORTA_BASE, GPIO_PIN_3);

    //
    // Configure the GPIO Pin Mux for PA2
	// for SSI0CLK
    //
	MAP_GPIOPinConfigure(GPIO_PA2_SSI0CLK);
	MAP_GPIOPinTypeSSI(GPIO_PORTA_BASE, GPIO_PIN_2);

    //
    // Configure the GPIO Pin Mux for PD4
	// for T3CCP0
    //
	MAP_GPIOPinConfigure(GPIO_PD4_T3CCP0);
	MAP_GPIOPinTypeTimer(GPIO_PORTD_BASE, GPIO_PIN_4);

    //
    // Configure the GPIO Pin Mux for PJ0
	// for U3RX
    //
	MAP_GPIOPinConfigure(GPIO_PJ0_U3RX);
	MAP_GPIOPinTypeUART(GPIO_PORTJ_BASE, GPIO_PIN_0);

    //
    // Configure the GPIO Pin Mux for PJ1
	// for U3TX
    //
	MAP_GPIOPinConfigure(GPIO_PJ1_U3TX);
	MAP_GPIOPinTypeUART(GPIO_PORTJ_BASE, GPIO_PIN_1);

    //
    // Configure the GPIO Pin Mux for PB0
	// for U1RX
    //
	MAP_GPIOPinConfigure(GPIO_PB0_U1RX);
	MAP_GPIOPinTypeUART(GPIO_PORTB_BASE, GPIO_PIN_0);

    //
    // Configure the GPIO Pin Mux for PB1
	// for U1TX
    //
	MAP_GPIOPinConfigure(GPIO_PB1_U1TX);
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	MAP_GPIOPinTypeUART(GPIO_PORTN_BASE, GPIO_PIN_5);

    //
    // Configure the GPIO Pin Mux for PK0
	// for U4RX
    //
	MAP_GPIOPinConfigure(GPIO_PK0_U4RX);
	MAP_GPIOPinTypeUART(GPIO_PORTK_BASE, GPIO_PIN_0);

    //
    // Configure the GPIO Pin Mux for PK1
	// for U4TX
    //
	MAP_GPIOPinConfigure(GPIO_PK1_U4TX);
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
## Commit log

2017-11-19 First commit, bring in last years parts lbr and setting up blank files, Licence and readme
2017-11-24 TI Tiva datasheets
2017-11-24 Lbr: adding TM4C tqfp-128 part
2017-11-26 no message
2017-11-26 SIM900 datasheets
2018-03-25 adding sim parts
2018-03-25 started mk3 sim breakout
2018-04-06 adding the msp432e401
2018-04-07 started dev board 1
2018-04-07 parts tweak
2018-04-08 adding power parts
2018-04-08 adding power supply
2018-04-08 connecting some serial interfaces
2018-04-09 some more connections done
2018-04-10 adding magjack
2018-04-10 changing to cc3120miod
2018-04-10 all major connections done
2018-04-10 testpoints added
2018-04-10 a few single testpoints
2018-04-11 ready to start routing
2018-04-14 load of routing
2018-04-15 getting closer...
2018-04-15 load of routing again
2018-04-15 load of routing again again
2018-04-16 load of routing again again again
2018-04-25 adding extra audio paths
2018-04-26 getting close
2018-04-27 zero airwires
2018-04-27 some silk work
2018-04-29 finishing touches...
2018-04-29 some tweaks
2018-04-29 silk tweaks
2018-04-29 final prototype 1 (hopefully)
2018-05-11 adding part numbers
2018-05-13 adding final few farnell numbers
2018-05-16 Datasheet swap out
2018-05-16 Parts: Lots of work
2018-05-16 Initial shape and some layout ideas
2018-05-16 Drop in a few more parts and identified some options for Spk, MIC and antennas
2018-05-17 NIght 2
2018-05-21 Day 3
2018-05-22 Schematic should now have all the parts
2018-05-22 Tweaks for BOM
2018-05-22 Tweaks for BOM 2
2018-05-25 Bom based updates
2018-05-28 Connect some pins, try out TI Booster pack headers and add MIC disconnect
2018-05-29 Night 4, Swap out CC3120MOD for CC3130R Getting some routing done
2018-05-30 Added tmp102, swapped out TPS62, more routing
2018-05-31 Day 5? routing done for prototype
2018-05-31 Gerber tweaks
2018-05-31 Cam job, some datasheets, out of date pinmux project
2018-06-15 Schematic
2018-06-25 Lots of changes for the final board design
2018-06-25 Artwork images
2018-06-25 Datasheets, lots of them
2018-06-28 Final design before panel
2018-06-29 Final tweeks and panel as went to mfg
2018-07-01 Correct schematic pdfs
2018-07-30 tweaks from final panel layout
2018-07-30 DXF: outline + final artwork for case design
2018-08-21 Few DNP's and schematic for print
2018-08-28 Last few tweaks
2018-08-28 Big clean up
2018-08-28 SIM800 upload tool and firmware
2018-08-30 Add Battery datasheet
2018-09-09 rename battery datasheet so it can be checked out on windows, fixes #2
